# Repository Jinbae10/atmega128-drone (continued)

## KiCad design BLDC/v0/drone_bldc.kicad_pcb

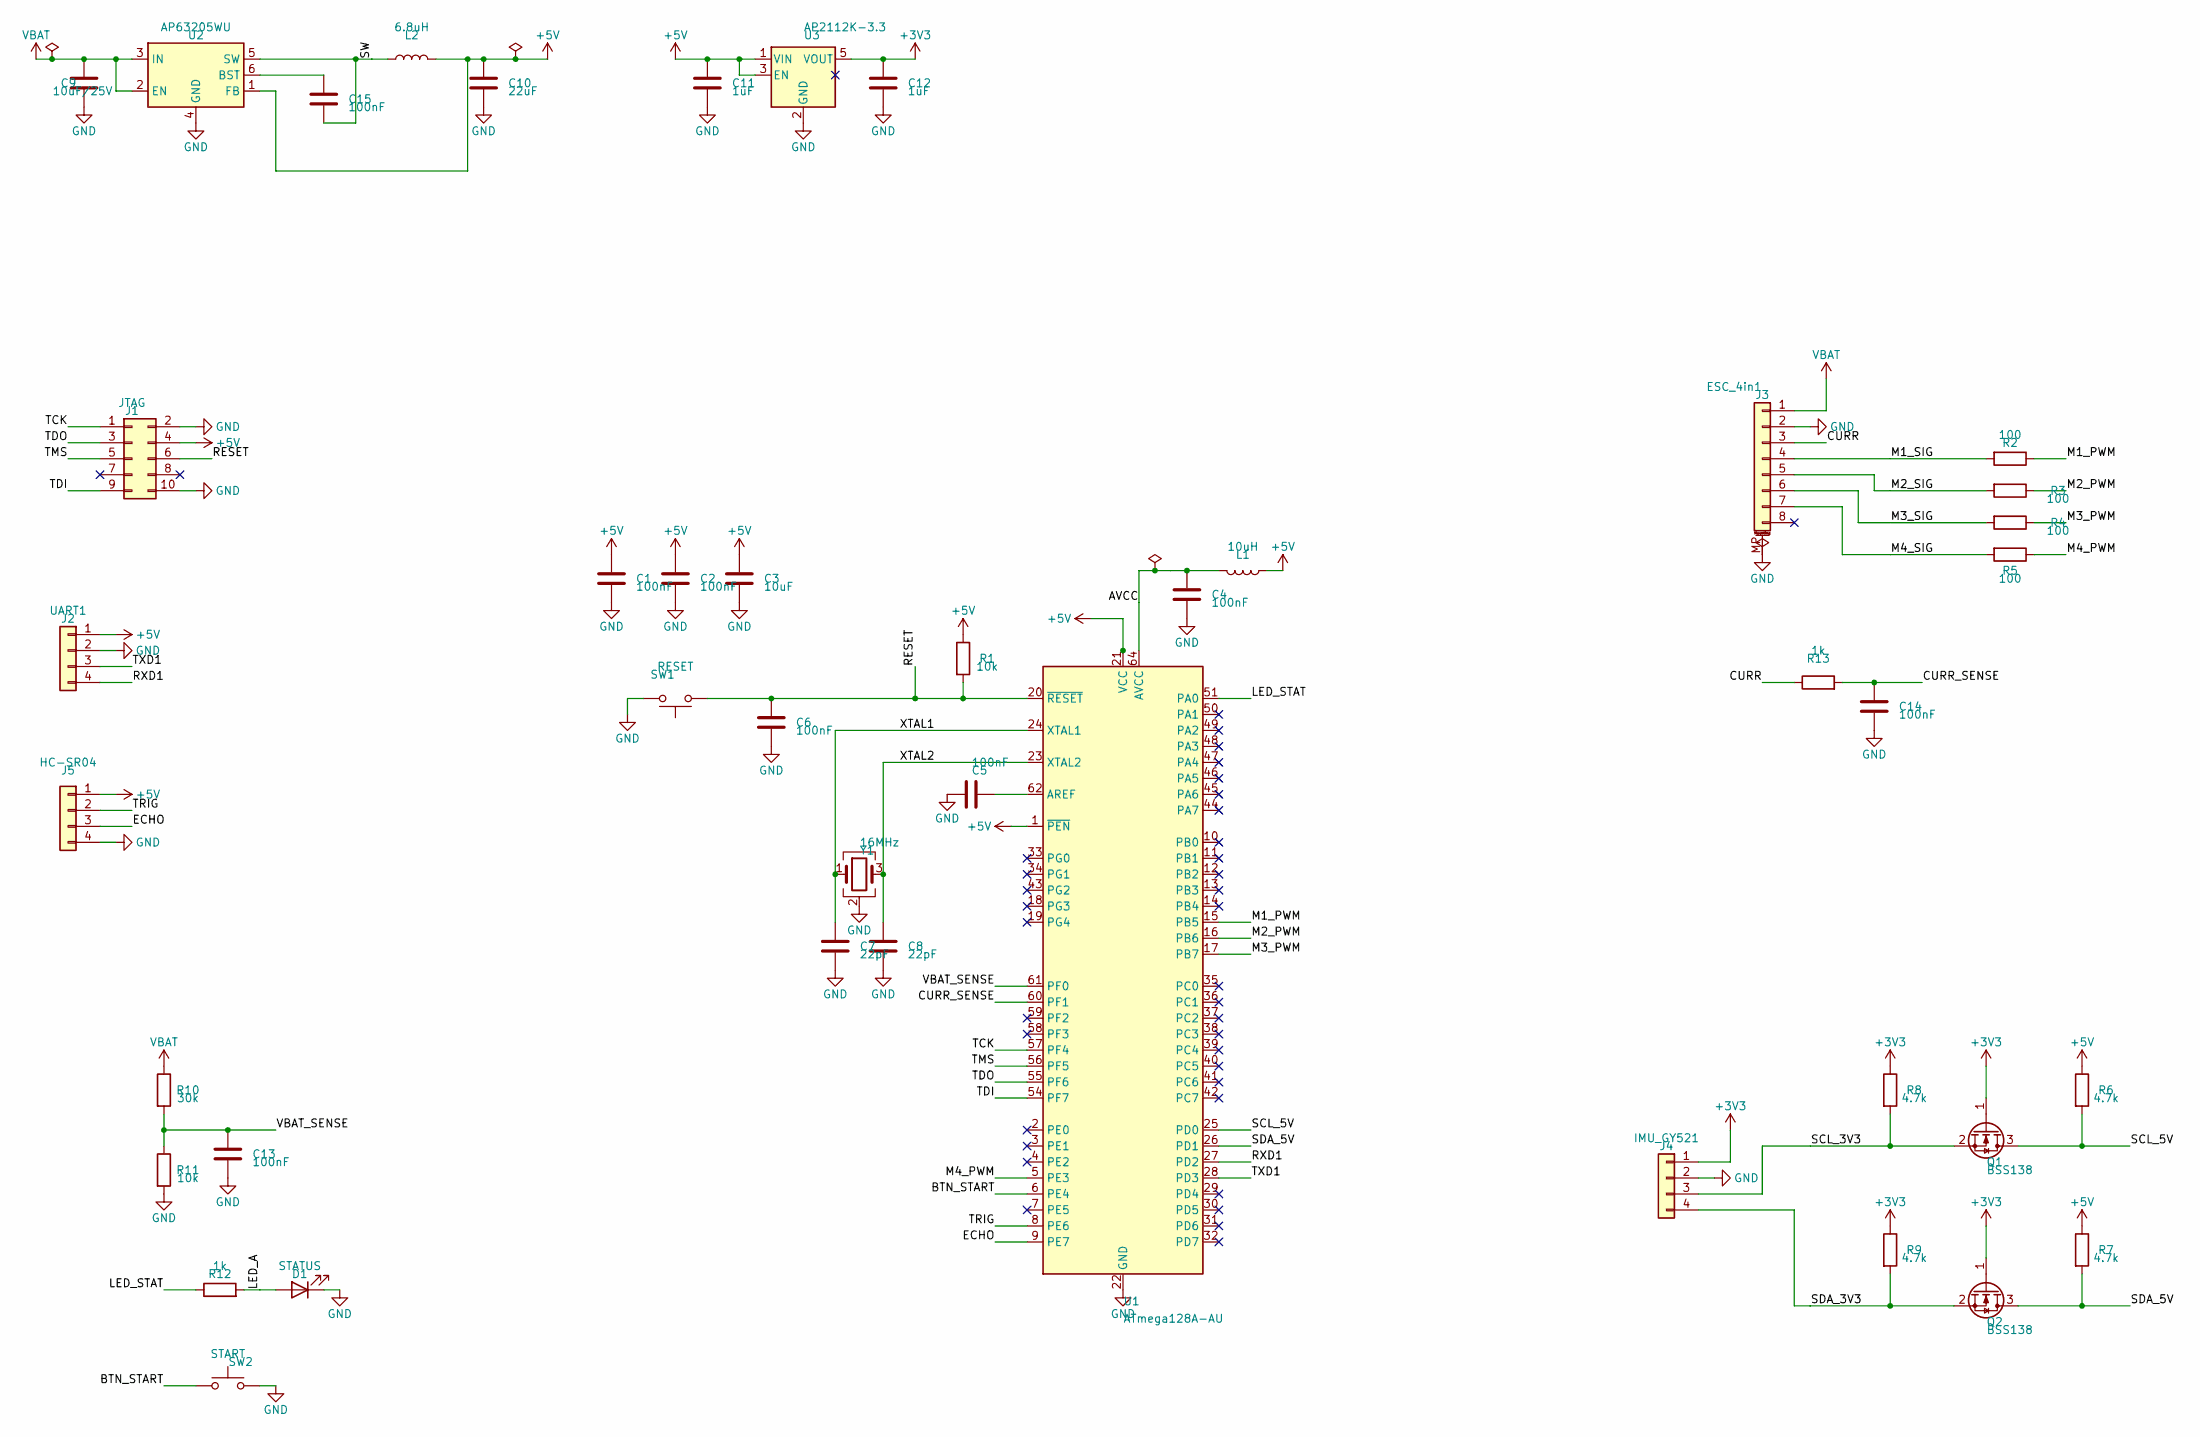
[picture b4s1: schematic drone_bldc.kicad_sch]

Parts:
C1, C2, C4, C5, C6, C13, C14, C15: 100nF; C_0603_1608Metric
C3: 10uF; C_0805_2012Metric
C7, C8: 22pF; C_0603_1608Metric
C9: 10uF/25V; C_0805_2012Metric
C10: 22uF; C_0805_2012Metric
C11, C12: 1uF; C_0603_1608Metric
D1: STATUS; LED_0603_1608Metric
J1: JTAG; PinHeader_2x05_P2.54mm_Vertical
J2: UART1; PinHeader_1x04_P2.54mm_Vertical
J3: ESC_4in1; JST_SH_SM08B-SRSS-TB_1x08-1MP_P1.00mm_Horizontal
J4: IMU_GY521; PinHeader_1x04_P2.54mm_Vertical
J5: HC-SR04; PinHeader_1x04_P2.54mm_Vertical
L1: 10uH; L_0805_2012Metric
L2: 6.8uH; L_Bourns-SRN4018
Q1, Q2: BSS138; SOT-23
R1, R11: 10k; R_0603_1608Metric
R2, R3, R4, R5: 100; R_0603_1608Metric
R6, R7, R8, R9: 4.7k; R_0603_1608Metric
R10: 30k; R_0603_1608Metric
R12, R13: 1k; R_0603_1608Metric
SW1: RESET; SW_SPST_TL3342
SW2: START; SW_SPST_TL3342
U1: ATmega128A-AU; TQFP-64_14x14mm_P0.8mm
U2: AP63205WU; TSOT-23-6
U3: AP2112K-3.3; SOT-23-5
Y1: 16MHz; Crystal_SMD_3225-4Pin_3.2x2.5mm

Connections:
+3V3: C12.1, J4.1, Q1.1 (G), Q2.1 (G), R8.1, R9.1, U3.5 (VOUT)
+5V: C1.1, C2.1, C3.1, C10.1, C11.1, J1.4, J2.1, J5.1, L1.1, L2.2, R1.1, R6.1, R7.1, U1.1 (~PEN), U1.21 (VCC), U1.52 (VCC), U2.1 (FB), U3.1 (VIN), U3.3 (EN)
AVCC: C4.1, L1.2, U1.64 (AVCC)
BTN_START: SW2.1, U1.6 (PE4)
CURR: J3.3, R13.1
CURR_SENSE: C14.1, R13.2, U1.60 (PF1)
ECHO: J5.3, U1.9 (PE7)
GND: C1.2, C2.2, C3.2, C4.2, C5.2, C6.2, C7.2, C8.2, C9.2, C10.2, C11.2, C12.2, C13.2, C14.2, D1.1 (K), J1.2, J1.10, J2.2, J3.2, J3.MP (MountPin), J4.2, J5.4, R11.2, SW1.2, SW2.2, U1.22 (GND), U1.53 (GND), U1.63 (GND), U2.4 (GND), U3.2 (GND), Y1.2 (G), Y1.4 (G)
LED_A: D1.2 (A), R12.2
LED_STAT: R12.1, U1.51 (PA0)
M1_PWM: R2.1, U1.15 (PB5)
M1_SIG: J3.4, R2.2
M2_PWM: R3.1, U1.16 (PB6)
M2_SIG: J3.5, R3.2
M3_PWM: R4.1, U1.17 (PB7)
M3_SIG: J3.6, R4.2
M4_PWM: R5.1, U1.5 (PE3)
M4_SIG: J3.7, R5.2
unnamed: C5.1, U1.62 (AREF)
unnamed: C15.1, U2.6 (BST)
RESET: C6.1, J1.6, R1.2, SW1.1, U1.20 (~RESET)
RXD1: J2.4, U1.27 (PD2)
SCL_3V3: J4.3, Q1.2 (S), R8.2
SCL_5V: Q1.3 (D), R6.2, U1.25 (PD0)
SDA_3V3: J4.4, Q2.2 (S), R9.2
SDA_5V: Q2.3 (D), R7.2, U1.26 (PD1)
SW: C15.2, L2.1, U2.5 (SW)
TCK: J1.1, U1.57 (PF4)
TDI: J1.9, U1.54 (PF7)
TDO: J1.3, U1.55 (PF6)
TMS: J1.5, U1.56 (PF5)
TRIG: J5.2, U1.8 (PE6)
TXD1: J2.3, U1.28 (PD3)
VBAT: C9.1, J3.1, R10.1, U2.2 (EN), U2.3 (IN)
VBAT_SENSE: C13.1, R10.2, R11.1, U1.61 (PF0)
XTAL1: C7.1, U1.24 (XTAL1), Y1.1
XTAL2: C8.1, U1.23 (XTAL2), Y1.3

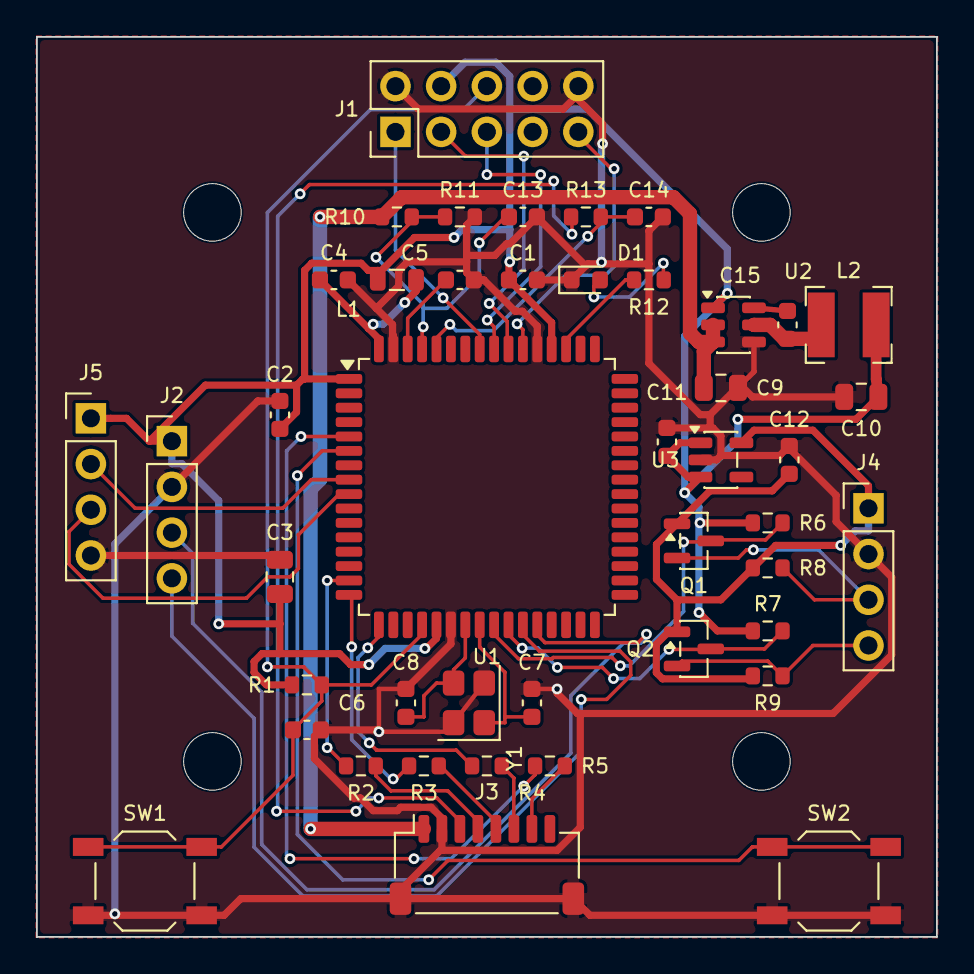
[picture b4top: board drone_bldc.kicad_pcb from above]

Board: 2 copper layers, 50.0 x 50.0 mm, 48 parts (0 on the bottom side), 37 nets.

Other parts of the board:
H1, H2, H3, H4: MountingHole_3.2mm_M3

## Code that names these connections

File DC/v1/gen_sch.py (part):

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    return '\n'.join(s)

# AT128A-70B V2.0 header, viewed from top (AT128A-70B_V20_data.md 4장). Left row = pins 1..29, right row = 30..58
L_ROW = ["/PEN", "PE0", "PE1", "PE2", "PE3", "PE4", "PE5", "PE6", "PE7", "VCC",
         "PB0", "PB1", "PB2", "PB3", "PB4", "PB5", "PB6", "PB7", "PG3", "PG4", "GND",
         "PD0", "PD1", "PD2", "PD3", "PD4", "PD5", "PD6", "PD7"]
R_ROW = ["PF0", "PF1", "PF2", "PF3", "PF4", "PF5", "PF6", "PF7", "/RST", "GND",
         "PA0", "PA1", "PA2", "PA3", "PA4", "PA5", "PA6", "PA7", "PG2", "PG1", "PG0",
         "PC7", "PC6", "PC5", "PC4", "PC3", "PC2", "PC1", "PC0"]
ptype = lambda n: 'power_in' if n in ('VCC', 'GND') else 'bidirectional'
PROJ_SYMS = {
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flag(P("C3", "1"), (G * 2, 0))
flag(P("C3", "2"), (G * 2, 0))                                   # GND flag

# VBAT sense divider -> PF0 (ADC0)
texts.append((20.32, 66.04, "VBAT sense: 10k/10k -> PF0 (ADC0), 4.2V -> 2.1V"))
part("Device:R", "R1", "10k", FP_R, 35.56, 74.93, {"1": "VBAT", "2": "-"})
part("Device:R", "R2", "10k", FP_R, 35.56, 87.63, {"1": "-", "2": "GND"})
part("Device:C", "C4", "100nF", FP_C, 45.72, 85.09, {"1": "-", "2": "GND"})
node = at(35.56, 81.28)
W(P("R1", "2"), node, P("R2", "1"))
W(node, P("C4", "1"), at(55.88, 81.28))
labels.append(("VBAT_SENSE", 55.88, 81.28, 0))

# ================= MOTOR DRIVERS x4 =================
texts.append((20.32, 116.84, "MOTOR DRIVER x4: SI2302 low-side, SS14 flyback across motor, gate 100R series + 10k pulldown"))
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
# ================= MCU MODULE =================
texts.append((248.92, 38.1, "MCU: AT128A-70B V2.0 on 2x 1x29 female headers (do not solder the module)\n"
                            "PF4-PF7 = JTAG (onboard 4.7k pullups), PE0/PE1/PB1 = ISP -> left unused"))
SIG = {"PE3": "M4_PWM", "PE4": "ECHO", "PE5": "TRIG", "PE6": "IMU_INT", "VCC": "+5V",
       "PB5": "M1_PWM", "PB6": "M2_PWM", "PB7": "M3_PWM",
       "PD0": "SCL", "PD1": "SDA", "PD2": "RXD1", "PD3": "TXD1", "PF0": "VBAT_SENSE", "GND": "GND"}
mods = {}
for i, n in enumerate(L_ROW): mods[str(i + 1)] = SIG.get(n)
for i, n in enumerate(R_ROW): mods[str(i + 30)] = SIG.get(n)
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texts.append((243.84, 111.76, "C5/C6: bulk + decoupling\nat module VCC header"))
texts.append((332.74, 132.08,
              "PIN MAP\n"
              "PB5/PB6/PB7 = OC1A/B/C -> M1/M2/M3 PWM\n"
              "PE3 = OC3A -> M4 PWM\n"
              "PE4 = INT4 <- ECHO,  PE5 -> TRIG\n"
              "PE6 = INT6 <- MPU-6050 INT\n"
              "PD0/PD1 = SCL/SDA (TWI)\n"
              "PD2/PD3 = RXD1/TXD1 (USART1, also module USART conn)\n"
              "PF0 = ADC0 <- VBAT/2\n\n"
              "WIRED BACKUP (AR-UART2USB): plug into the module's own\n"
              "USART connector (same USART1). Remove HC-06 first and\n"
              "leave the red 5V wire unconnected (board has its own 5V)."))
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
